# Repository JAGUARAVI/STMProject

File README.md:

# ESWCap — STM32G474

Port of the **ESWCap** autoranging capacitance meter (originally ESP32-S3 / ESP-IDF)
to an **STM32G474CEU6**, targeting the **WeAct Studio "Long" core board**.

> **Status: firmware implemented, not yet run on silicon.** C-mode (RC-step +
> comparator oscillator), autoranging, fusion, calibration, the console and the
> `@@EVT` protocol are complete. R-mode (Kelvin/TIA) is implemented for the
> combined board and is compile-time gated behind `ESWCAP_HAS_RMODE`; the
> default build refuses `mode r` until the Q1/LMC6482/K1/K2/OPAMP3 hardware is
> fitted. See `docs/handoff-verdict.md` for the topology review and
> `docs/port-plan.md` §6 for bring-up.

---

## Target hardware

| Property | Value |
| --- | --- |
| Board | WeAct Studio STM32G474CEU6 "Long" core board |
| MCU | STM32G474CEU6 — Cortex-M4F, 170 MHz |
| Package | UFQFPN48 (48 pins) |
| Flash | 512 KB |
| SRAM | 128 KB |
| HSE crystal | 8 MHz, on **PF0/PF1** (not PA) |
| Regulator | ME6231A33M3G (5 V pin accepts ~3.5–18 V) |
| User LED | **PC6**, active high (`PC6 -> 5.1k -> LED -> GND`) |
| User button | **PC13**, active **high** (`PC13 -> 330R -> key -> 3.3 V`) |

Board repo (schematics, datasheets, examples):
<https://github.com/WeActStudio/WeActStudio.STM32G474CoreBoard>

### Carrier PCB (Rev B)

The combined C+R front end is built as a 111 × 85 mm, 2-layer carrier under the
WeAct Long module.  The module plugs into two rows of 2.54 mm sockets; the
analog front end, relays, SSRs, DUT/bias terminals and console header are on the
carrier.

| Item | Value |
| --- | --- |
| Schematic | `~/Documents/KiCad/Project/Project.kicad_sch` (KiCad 10) |
| PCB | `~/Documents/KiCad/Project/Project.kicad_pcb` |
| Fab outputs | `~/Documents/KiCad/Project/fab/` (Gerbers, drill, BOM, PnP) |
| Design record | [`docs/pcb-design.md`](docs/pcb-design.md) |
| DRC | 0 errors, 0 unconnected, 25 silkscreen-only warnings |
| Module pin order | P1/P2 pin 1 at the **right** end; P3/P4 four leftmost pins |
| Rev B fixes | D6 body-diode block, C1 35 V bipolar, R9 47 Ω, C3 to VREF, console J7, per-IC decoupling, fail-safe pulls |

The module's +5 V comes from USB VBUS (P3-4); the relay coils need USB power.

### Peripheral availability on the 48-pin package

Verified against the STM32G474CE pin database (UFQFPN48). The analog peripherals
are **better** here than the 48-pin pin count suggests — the earlier assumption
that the internal analog is unusable was wrong.

**Comparators — all 7 are bonded out.** Each `INM` can be driven internally by a
DAC, so the comparator reference needs no external divider.

| | `INP` | `INM` options | Internal DAC on `INM` | Output pins (AF8) |
| --- | --- | --- | --- | --- |
| COMP1 | PA1, PB1 | PA0, PA4 | **DAC1_CH1, DAC3_CH1** | PA0, PA6, PA11, PB8 |
| COMP2 | PA3, PA7 | PA2, PA5 | **DAC1_CH2, DAC3_CH2** | PA2, PA7, PA9, PA12 |
| COMP3 | PA0 | PF1 *(HSE!)* | DAC1_CH1, DAC3_CH1 | PB7, PB15 (AF3) |
| COMP4 | PB0 | PB2 | **DAC1_CH1, DAC3_CH2** | PB1, PB6, PB14 |
| COMP5 | PB13 | PB10 | DAC1_CH2, DAC4_CH1 | PA9 |
| COMP6 | PB11 | PB15 | DAC2_CH1, DAC4_CH2 | PA10, PC6 (AF7) |
| COMP7 | PB14 | PB12 | DAC2_CH1, DAC4_CH1 | PA8 |

**OPAMPs — 1, 2 and 3 are bonded out** (USB is on PA11/PA12, not PA2/PA3).
`InternalOutput` routes `VOUT` straight to an ADC channel with **no pin**:

| | `VINP` | Internal `VINP` | `VINM` | `VOUT` pin | `VOUT`→ADC (internal) |
| --- | --- | --- | --- | --- | --- |
| OPAMP1 | PA1, PA3, PA7 | **DAC3_CH1** | PA3 | PA2 | ADC1_IN13 |
| OPAMP2 | PA7, PB14, PB0 | — | PA5 | PA6 | ADC2_IN16 |
| OPAMP3 | PB0, PB13, PA1 | **DAC3_CH2** | PB2, PB10 | PB1 | ADC2_IN18, ADC3_IN13 |

OPAMP4/5/6 need PD/PE pins that do not exist on the 48-pin package.

**ADCs** — 5 instances, channels available:

* `ADC1`: PA0(IN1), PA1(IN2), PA2(IN3), PA3(IN4), PB0(IN15), PB1(IN12),
  PB11(IN14), PB12(IN11), PB14(IN5), PF0(IN10)
* `ADC2`: PA0(IN1), PA1(IN2), PA4(IN17), PA5(IN13), PA6(IN3), PA7(IN4),
  PB11(IN14), PB15(IN15), PB2(IN12), PC4(IN5), PF1(IN10)
* `ADC3`: PB0(IN12), PB1(IN1), PB13(IN5)
* `ADC4`: PB12(IN3), PB14(IN4), PB15(IN5)
* `ADC5`: PA8(IN1), PA9(IN2)

**DAC — 4 instances, but only DAC1/DAC2 have pins:**

| | Pin output | Internal-only use | Max rate |
| --- | --- | --- | --- |
| DAC1 | `OUT1 = PA4`, `OUT2 = PA5` | COMP1/3/4, COMP2/5 | 1 MSPS |
| DAC2 | `OUT1 = PA6` | COMP6/7 only | 1 MSPS |
| **DAC3** | **none** | **COMP1/3, COMP4, OPAMP1, OPAMP3, OPAMP6** | 15 MSPS |
| **DAC4** | **none** | COMP5/7, COMP6, OPAMP4, OPAMP5 | 15 MSPS |

**DAC3/DAC4 are internal-only by design** — they exist purely to feed comparators
and op-amps with no pin at all. That is a significant asset for this project:
**two extra 12-bit threshold sources at zero pin cost.** Prefer them for the
comparator reference so PA4/PA5 stay free.

**Reference:** pin 20 is a dedicated **`VREF+`** — a clean external reference can
be fitted instead of relying on VDDA. `VREFBUF` (2.048 / 2.5 / 2.9 V) is also
available but draw only ~6.5 mA and needs 1 µF + 100 nF at the pin.

#### Comparator → timer routing (the key capability)

A comparator output can reach a timer's input capture **internally, with no pin**.
This is what lets the ESP32's software ISR be replaced by hardware period
measurement. Routing flexibility differs sharply by timer:

| Timer | Width | COMPs accepted on `TI1` | Notes |
| --- | --- | --- | --- |
| **TIM2** | **32-bit** | **COMP1…COMP7** | Best choice: no overflow bookkeeping to 25 s |
| TIM3 | 16-bit | COMP1…COMP7 | Also very flexible |
| TIM4 | 16-bit | COMP1…COMP7 | |
| TIM1/TIM8/TIM20 | 16-bit | COMP1…COMP4 only | `TI2/3/4` accept no comparator |

**Recommendation: `COMP1_OUT` → `TIM2_CH1` input capture.** TIM2 is 32-bit, accepts
any comparator on `TI1`, and at 170 MHz gives 5.88 ns resolution with a 25.3 s
wrap — covering the whole 10 Hz…1 MHz oscillator band in one timer, unpowered by
CPU jitter.

#### Real constraints to plan around

* **`INM` and the DAC output share pins.** `PA4` is both `DAC1_OUT1` and
  COMP1's `INM`; `PA5` is both `DAC1_OUT2` and COMP2's `INM`. Using the internal
  DAC costs those pins. **Use DAC3 instead** to avoid the conflict entirely.
* **Comparator output must not land on its own input pin.** COMP1's output
  shares PA0 with its `INM`; COMP2's shares PA2 with its `INM`. Pick a different
  output (COMP2 → PA7/PA9) — or better, route it internally to the timer and use
  **no output pin at all**. COMP1's output exists **only on PA0, PA6, PA11 and
  PB8** (not PA8 — PA8's AF8 is COMP7_OUT). PA11 is USB and PB8 is BOOT0, so
  in practice it is PA0 or PA6.
* **OPAMP1 `VOUT` (PA2) overlaps COMP2's `INM`**, and OPAMP2 `VOUT` (PA6)
  overlaps COMP1's output. Mode-dependent, but allocate deliberately.
* **`OPAMP_NONINVERTINGINPUT_DAC` and `..._IO3` are the same bit encoding**
  (`OPAMP_CSR_VPSEL`). Which one is active is per-instance. Set it deliberately.
* **No OPAMP→OPAMP and no OPAMP→COMP internal chaining** on G4. Internal chains
  are only `DAC→COMP`, `DAC→OPAMP`, `OPAMP→ADC`.
* **No `DAC→ADC` direct channel.** To read a DAC internally, route it through an
  op-amp: `DAC3_CHx → OPAMP(follower) → ADC` (all internal).
* **No comparator window mode on G4** (contrary to many blog posts) and **no
  clocked comparator output filter** — only programmable hysteresis and
  timer-based blanking.
* **COMP3's only `INM` is `PF1`, which is the HSE crystal pin.** COMP3 is
  effectively unusable while the external crystal is fitted.
* **Reserved:** PA13/PA14 (SWD), PC6 (user LED), PC13 (user button),
  PF0/PF1 (HSE crystal), PA11/PA12 (USB D−/D+), PB8 (BOOT0).

### Replacing the LM393 with COMP1 — strongly recommended

The external LM393 oscillator can be replaced by **COMP1** entirely. The
comparator's `INM` can be driven by `DAC1_CH1` internally, so the external
reference divider (10 kΩ/10 kΩ), the 100 kΩ hysteresis resistor and the 10 kΩ
pull-up all disappear with the chip.

Suggested mapping (avoiding the collisions above):

| Function | Pin | Notes |
| --- | --- | --- |
| COMP1 `INP` | **PB1** | `V_cap` sense node (BAT54S clamped) |
| COMP1 `INM` | internal | `DAC1_CH1` — replaces the 1.65 V divider |
| `DAC1_OUT1` | PA4 | leave unrouted, or reserve |
| COMP1 `OUT` | **PA0** or **PA6** | drive-buffer input; timer capture is internal |

Why this is an upgrade, not just a part-count reduction:

* **Programmable hysteresis.** The LM393's hysteresis is fixed by the 100 kΩ
  feedback resistor. COMP1 sets hysteresis on a 0–1023 scale in software, so it
  can be tuned **per range** instead of one compromise value.
* **Timer input-capture replaces the ISR.** Route `COMP1_OUT` to a timer's
  capture input and the period is measured in hardware. This directly addresses
  the *"ISR Latency Profiling"* pending item in the ESP32 `HANDOVER.md` — the
  ESP32's software oscillator loop put CPU jitter straight into the timing.
* **The rate limiter becomes unnecessary.** `OSC_MIN_EDGE_INTERVAL_US = 3`
  exists because the ESP32 ISR had to mirror the comparator output back to the
  drive pin, so a too-fast loop could freeze the device. With COMP1 driving the
  timing directly, a too-fast loop self-limits rather than hanging the CPU.
* **Far faster.** G4 comparator propagation is ns-class versus the LM393's
  ~1.3 µs, which is what actually limited the sub-100 pF ranges.

This does not change the *physics* of `T = K·R·C + T0`, so the existing `K`/`T0`
calibration model carries over unchanged.

---

## Toolchain

| Component | Version / location |
| --- | --- |
| PlatformIO Core | 6.2.0 — `~/.platformio/penv/bin/pio` |
| STM32 platform | `ststm32` 20.0.0 |
| Framework | **STM32Cube HAL/LL** (`framework = stm32cube`) |
| Toolchain | `arm-none-eabi-gcc` 7.2.1 (installed by PlatformIO) |
| Upload | **USB DFU** bootloader via `dfu-util` |
| Debug | Optional — ST-Link / SWD (see below) |

PlatformIO Core is installed under `~/.platformio/penv` and is **not on the
default PATH**. The project's `.vscode/settings.json` prepends it for integrated
terminals. For your own shell:

```bash
export PATH="$HOME/.platformio/penv/bin:$PATH"
```

---

## Build, upload, monitor

```bash
pio run                      # build (default env: weact_g474ceu6)
pio run -t upload            # flash over USB DFU
pio device monitor -b 115200 # serial console, USART1 on PA9/PA10
```

> **Console wiring:** the WeAct Long board has **native USB only** (PA11/PA12);
> there is no on-board USB-UART bridge. The Type-C port is for DFU/programming.
> For the console, connect an external 3.3 V USB-UART adapter to the P1 header:
> adapter TX -> **PA10**, adapter RX -> **PA9**, GND -> GND. Do not connect the
> adapter's 3.3 V if the board is already powered.

### Flashing over USB DFU

The board ships with ST's ROM DFU bootloader. No probe is required.

1. Hold **BOOT0**, then tap **NRST**, then release **BOOT0**.
2. The board enumerates as ST's ROM bootloader — USB ID `0483:DF11`.
3. Run `pio run -t upload`. PlatformIO adds the DFU suffix to `firmware.bin`
   automatically and flashes it with `dfu-util`.
4. Reset (or power-cycle) to run the firmware.

Check the device is visible:

```bash
lsusb | grep -i 0483        # expect: 0483:df11 STMicroelectronics STM32 BOOTLOADER
dfu-util -l                 # lists DFU interfaces
```

If `dfu-util` reports no device, the board is not in DFU mode, or the udev rules
do not grant access (see **udev** below).

### Debugging over SWD (optional)

DFU cannot debug. To single-step, watch variables or use breakpoints, attach a
probe to the SWD header and use the debug environment:

```bash
pio run  -e weact_g474ceu6_debug -t upload   # upload over SWD
pio debug -e weact_g474ceu6_debug            # start a debug session
```

This env is built with `-DDEBUG -DUSE_FULL_ASSERT` and flashes via `stlink`.

---

## Environments

| Environment | Framework | Upload | Purpose |
| --- | --- | --- | --- |
| `weact_g474ceu6` | stm32cube | **dfu** | Default. C-mode-only build; flash over USB. |
| `weact_g474ceu6_debug` | stm32cube | stlink | `-DDEBUG -DUSE_FULL_ASSERT`, for GDB/Live Watch. |
| `weact_g474ceu6_stlink` | ststm32 | stlink | Release build, flashed via an SWD probe. |
| `weact_g474ceu6_combined` | stm32cube | dfu | `-DESWCAP_HAS_RMODE=1`; requires the Q1/LMC6482/K1/K2/OPAMP3 front end. |

The combined board is a **compile-time** choice on purpose: the default build
must not energise relay coils or drive a Q1 gate that is not fitted. `mode r`
refuses with a clear message until `ESWCAP_HAS_RMODE=1`.

---

## IDE setup

The project is configured for **VS Code** (and compatible forks).

1. Install the recommended extensions — VS Code prompts on open, or run
   *Extensions: Show Recommended Extensions*:
   * `platformio.platformio-ide` (required)
   * `ms-vscode.cpptools` (required by PlatformIO IDE for IntelliSense)
2. Open this folder. PlatformIO indexes the project and writes
   `.vscode/c_cpp_properties.json`, which supplies all Cube HAL include paths
   and the `STM32G474xx` define automatically.
3. Build once (`pio run`) to populate IntelliSense and the compile database.

`.vscode/settings.json` is committed and already handles:

* `pio` on the integrated-terminal PATH,
* C standard / IntelliSense mode (`gcc-arm`),
* serial monitor defaults (115200, DTR/RTS de-asserted),
* excluding `.pio/` from search and the explorer.

`.vscode/c_cpp_properties.json` is gitignored — it is regenerated by PlatformIO
after each build and contains absolute paths. `.vscode/launch.json` **is**
committed, because DFU cannot debug and so PlatformIO never generates it for
this setup.

### udev rules (Linux, for DFU and probes)

PlatformIO's own rules file is already installed at
`/etc/udev/rules.d/99-platformio-udev.rules`, which covers ST-Link and the STM32
DFU bootloader. If `dfu-util` cannot open the device, reinstall them:

```bash
curl -fsSL https://raw.githubusercontent.com/platformio/platformio-core/develop/platformio/assets/system/99-platformio-udev.rules \
  | sudo tee /etc/udev/rules.d/99-platformio-udev.rules
sudo udevadm control --reload-rules && sudo udevadm trigger
```

Then unplug/replug the board. Note this system has no `plugdev` group; if access
still fails, add a rule scoped to your user or group.

---

## Firmware architecture

The ESP32 build was 4 000 lines in one file. This port splits it so the maths is
testable on a host and the hardware access is confined to one layer.

```
src/
  main.c              entry point (nothing else)
  app.c               cooperative scheduler: the only place that decides when to measure
  bsp/                hardware layer — the only code that touches HAL/registers
    bsp.c             170 MHz PLL from HSE, SysTick, DWT, IWDG, USB clock
    bsp_console.c     USART1 interrupt-driven RX, line assembly, printf
    bsp_adc.c         ADC1 stream (TIM6+DMA+oversampling), ADC2/3/4 single reads, VREFINT
    bsp_comp.c        COMP1 + DAC3 + TIM2 TISEL capture; COMP4 overvoltage guard
    bsp_frontend.c    SSR/relay/mux control, safety state machine, mode interlock
    bsp_dac.c         DAC3_CH1 (COMP1) and DAC1_CH1 (COMP4), both internal-only
    bsp_opamp.c       OPAMP1: R-mode Kelvin error amplifier (VINP=B, VINM=VREF)
    bsp_opamp3.c      OPAMP3: V_N unity-gain buffer
    bsp_store.c       flash record store (NVS replacement)
    bsp_led.c         PC6 software-PWM status LED
  measure/            pure arithmetic — no HAL, host-testable
    rc_fit.c          voltage-domain Gauss-Newton exponential fit
    osc_calc.c        T = K*R*C + T0 model and its solvers
    board.c           board constants and the C_block series transform
    adc_measure.c     curve -> scored sample (fit, gates, quality)
    osc_measure.c     period -> scored sample
    fusion.c          median gate and log-domain weighted fusion
    autorange.c       PROBE -> SWEEP -> FUSION pipeline
    rmode.c           4-wire Kelvin / TIA resistance (BSP-facing)
    rmode_math.c      pure Kelvin/TIA arithmetic (host-tested)
  calib/calib.c       calibration state, solvers, flash record
  proto/
    events.c          @@EVT JSON telemetry (contract preserved)
    console_cmds.c    the command set
```

What the hardware changed, relative to the ESP32:

| ESP32 mechanism | G474 mechanism |
| --- | --- |
| Software ADC poll loop + adaptive decimation | TIM6-triggered ADC1 + circular DMA, hardware oversampling |
| LM393 + 10k/10k divider + 100k hysteresis | COMP1 + DAC3 internal threshold (70 mV hysteresis, K ≈ 0.085) |
| ISR mirrors comparator, PCNT measures it | **No CPU in the loop**: COMP1_OUT/PA0 drives the buffer; TIM2 captures via TISEL |
| NVS blob store | reserved 2 KB flash page, append-only CRC records |
| WS2812 over RMT | PC6 software PWM, same operational language |

## Testing

The measurement maths compiles and runs on the build machine:

```bash
make -C test/host        # builds and runs the unit tests
```

21 tests cover the exponential fit (including its insensitivity to a biased
asymptote), the C_block transform, the oscillator model and two-point solve, ADC
and oscillator sample scoring, fusion gating and log-domain averaging, both
calibration solvers, the Kelvin/TIA resistance equations, and the R-mode
calibration setters. They run against
the **same source files** the firmware uses; only the flash store is stubbed.

---

## Repository layout

```
platformio.ini          Build/upload/debug configuration (3 environments)
src/main.c              Entry point
src/app.c               Scheduler
src/bsp/                Hardware layer
src/measure/            Measurement maths (HAL-free)
src/calib/              Calibration state and solvers
src/proto/              Telemetry and console
include/                Public headers, pin map (config.h), stm32_assert.h
test/host/              Host unit tests (make -C test/host)
docs/                   Port plan, peripheral reference, design notes
.vscode/                Editor configuration
```

---

## Documentation

| Document | Purpose |
| --- | --- |
| **`docs/port-plan.md`** | **The port plan.** Audit of the ESP32 firmware, the G474 architecture it maps to, the document rework list, and the phased build sequence. Start here. |
| **`docs/peripherals-g474.md`** | Verified peripheral facts — ADC/COMP/DAC/OPAMP/timer/storage, plus the ES0430 errata that constrain the code. |
| **`docs/handoff-verdict.md`** | **Review of the other agent's handoff**: what it gets right, what is unsafe to apply literally, what the previous firmware got wrong, and the corrected pin map. Read with the R-mode work. |
| `docs/kelvin-ohmmeter-g474.md` | R-mode electrical design. Superseded banner + corrected topology, pin map and equations. |
| `docs/resistance-autoranging-plan.md` | R-mode autoranging + Kelvin/TIA topology. The topology is adopted; the pin table is corrected by the verdict. |

The two R-mode notes were written for a **100-pin G474VE**. They remain useful for
the *electrical* design (sensing topology, ratiometric maths, error budget,
interlock rules); their pin maps and internal-peripheral assumptions have been
corrected in place against the verified 48-pin data.

---

## Next steps

The firmware is complete; what remains needs the physical board.

1. **Verify the pin map against the actual front-end wiring.** `include/config.h`
   is the single source of truth. The switch polarities (SSR/relay active-high,
   MAX4619 EN active-low) are isolated behind three constants in
   `bsp_frontend.c`. The R-mode pins are only meaningful once the combined board
   is fitted.
2. **Flash and confirm the platform comes up.** Expect the banner, `SYSCLK
   170000000 Hz`, and a plausible `VDDA` reading. A blink-code loop at boot
   identifies which `require()` failed (1 = clocks … 8 = R-mode analog).
3. **Verify the ADC stream.** A known DC level on `V_cap` should read correctly,
   and the sample period should match the requested period (scope PA0 for the
   comparator, or trigger on a GPIO toggle).
4. **Verify the comparator.** Inject a square wave on the DUT node and confirm
   the console's `status`/`probe` see oscillation and that `zero` produces a
   stable `T0`. This is the step that proves `TISEL` routing works on silicon.
5. **Calibrate.** `mode c`, then `zero`, `cal1`/`cal2` with 1 % C0G/NP0
   references, `adccal1`/`adccal2` with film references. Record the new `T0`;
   it should be smaller than the ESP32 value because no ISR latency remains.
6. **R-mode bring-up.** Build `weact_g474ceu6_combined` (it sets
   `ESWCAP_HAS_RMODE=1`), flash, `discharge`, `mode r`, then `res`. Check
   V_B ~= 405 mV on a 1 kohm DUT before trusting the top element or the TIA.
   On a C-mode-only board the default build refuses `mode r` instead of
   energising relays that do not exist.

See `docs/port-plan.md` §6 for the phase-by-phase acceptance criteria and §7
for the risk list.

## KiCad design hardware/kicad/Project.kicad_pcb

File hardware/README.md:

# ESWCap Rev C.1 hardware

This directory contains the KiCad source for the Rev C carrier with the
accuracy-plan changes applied (**Rev C.1**, see `docs/accuracy-plan.md`):
USB-only power, 3.3 V relays, true 4-wire C/R, the corrected J8 bias header,
and the H1–H6 accuracy changes.

## Status (2026-11-13)

- **Schematic:** Rev C + accuracy plan H1–H6. ERC-clean (0 errors, 0 warnings).
  - H1 J2-13 (PA7, OPAMP1 sense) moved FL → `MUXR_COM`
  - H2 `MUXR_EN` moved J2-17 (PB2) → J1-17 (PB15)
  - H3 `VBUF` also on J2-17 (PB2, OPAMP3 VINM0) for the PGA stage
  - H4 R20 100k → 1k; H5 D1 BAT54S → BAV199; H6 R33 1M → 10M
  - PWR_FLAGs excluded from BOM/board
- **PCB:** `kicad/Project.kicad_pcb`, 111 × 85 mm, 2 layers, **fully routed**.
  DRC: 0 unconnected, 0 clearance/short/hole errors, schematic parity clean;
  45 silkscreen-only warnings. Critical analog nets are hand-routed and locked;
  the rest is Freerouting + targeted fixes. How it was built:
  `scripts/README.md`.
  - Ground: B.Cu plane + F.Cu pour, stitched by ~318 vias, with **no-pour
    cutouts** under J5/SH divider/U9/U10, the VCAP node, and the TIA input (P2)
  - TIA guard: F.Cu `VBIAS` pour around the U1A summing node (P1)
  - Footprint fixes: C1 and J5/J6 courtyards/silkscreen now match the real
    bodies (they were drawn around the pads only)
- **Fab outputs:** `fab/Project-gerbers.zip` (`fab/gerbers/`), drill + map,
  `fab/Project-pos.csv`, `fab/Project-bom.csv`, schematic PDF/SVG,
  `fab/Project-pcb-front.pdf` / `-back.pdf`, `fab/Project-3d-top.png`.
  **Not yet reviewed by a person — review before ordering.**
- `wip/Project-revC-routing-baseline.kicad_pcb` is the old pre-review baseline,
  kept for reference only. Do not fabricate it.

Open `kicad/Project.kicad_pro` with KiCad 10. The project-local libraries
(`eswcap.kicad_sym`, `eswcap.pretty/`) are included; the schematic will not
resolve symbols/footprints without them.

## Rev C circuit summary

- **Power:** USB-C VBUS → module D4 → VDD5V → module ME6231A33M3G LDO → +3.3 V.
  J3-3/4 (`VDD5V`) are NC on the carrier. No 5 V carrier rail. Only Vbias
  (0–20 V) is external, on J6.
- **Relays:** K1/K2 = Omron **G6S-2 DC3** (3 V coils) on +3.3 V. D4/D5
  flyback cathodes, C10/C15, and coil high side are on +3V3.
- **DUT:** J5 is 4-pin, ordered **FH, SH, SL, FL**. R-mode is true 4-wire
  Kelvin; `SL` has a 100 kΩ series resistor (R40) into U1B.
- **C-mode 4-terminal sense:** 10 M/1 M divider on `SH` (R38/R39), compensated
  by C21 10 pF across the top leg and C20 100 pF across the bottom leg. The
  divider is buffered by the **internal STM32 OPAMP3** (no second LMC6482).
  U9 isolates the `SH → R20 → VN_SENSE` branch when K1 is off; U10 connects
  `SH_DIV` to `VN_SENSE` when K1 is off. U10 is controlled by PC4
  (`C_MODE_SW`, active low).
- **R20 / D2:** R20 = 100 kΩ; D2 = BAV199 (low-leakage clamp).
- **J8 bias-control header:**

| Pin | Signal | Module pin | Note |
| --- | --- | --- | --- |
| 1 | `BIAS_SET` | PA4 / J2-10 | TIM3_CH2 PWM, R34 1 k + C16 10 µF |
| 2 | `BIAS_EN` | PA15 / J1-10 | GPIO, R35 10 k pulldown |
| 3 | `BIAS_MON` | **PA8 / J1-15** | ADC5_IN1, R36 1 k + C17 100 nF |
| 4 | GND | — | — |
| 5 | `+3V3` | J4 | future module <50 mA |
| 6 | `BIAS_UART_TX` | PC10 / J1-9 | USART3_TX |
| 7 | `BIAS_UART_RX` | PC11 / J1-8 | USART3_RX |
| 8 | GND | — | — |

- **PA0 is `DRIVE` / COMP1_OUT** (firmware fix of 2026-11-12). PA8 is now free
  and carries `BIAS_MON`. PC4 is the U10 control output.
- **J5 pin order:** 1 FH, 2 SH, 3 SL, 4 FL. Use 1–2 and 3–4 links for a 2-wire
  DUT.

## BOM

`fab/Project-bom.csv` is generated from the schematic. It contains 88 physical
parts, 46 grouped lines and 3 PWR_FLAGs. The only new orderable part type is
J8 (1×8 2.54 mm header) and J5 (4-pin 5.08 mm terminal block); K1/K2 are
G6S-2 DC3. See the CSV for the complete list.

## What is deliberately not here

- The second LMC6482 was removed: it is not available. The C-mode SH divider
  now uses the internal OPAMP3.
- The PCB is not final. It must be regenerated and rerouted after the
  schematic is frozen. The WIP baseline has the pre-U9/U10 netlist and must
  not be fabricated.
- The OLED/button additions proposed in the integration-plan review are not
  part of this revision.

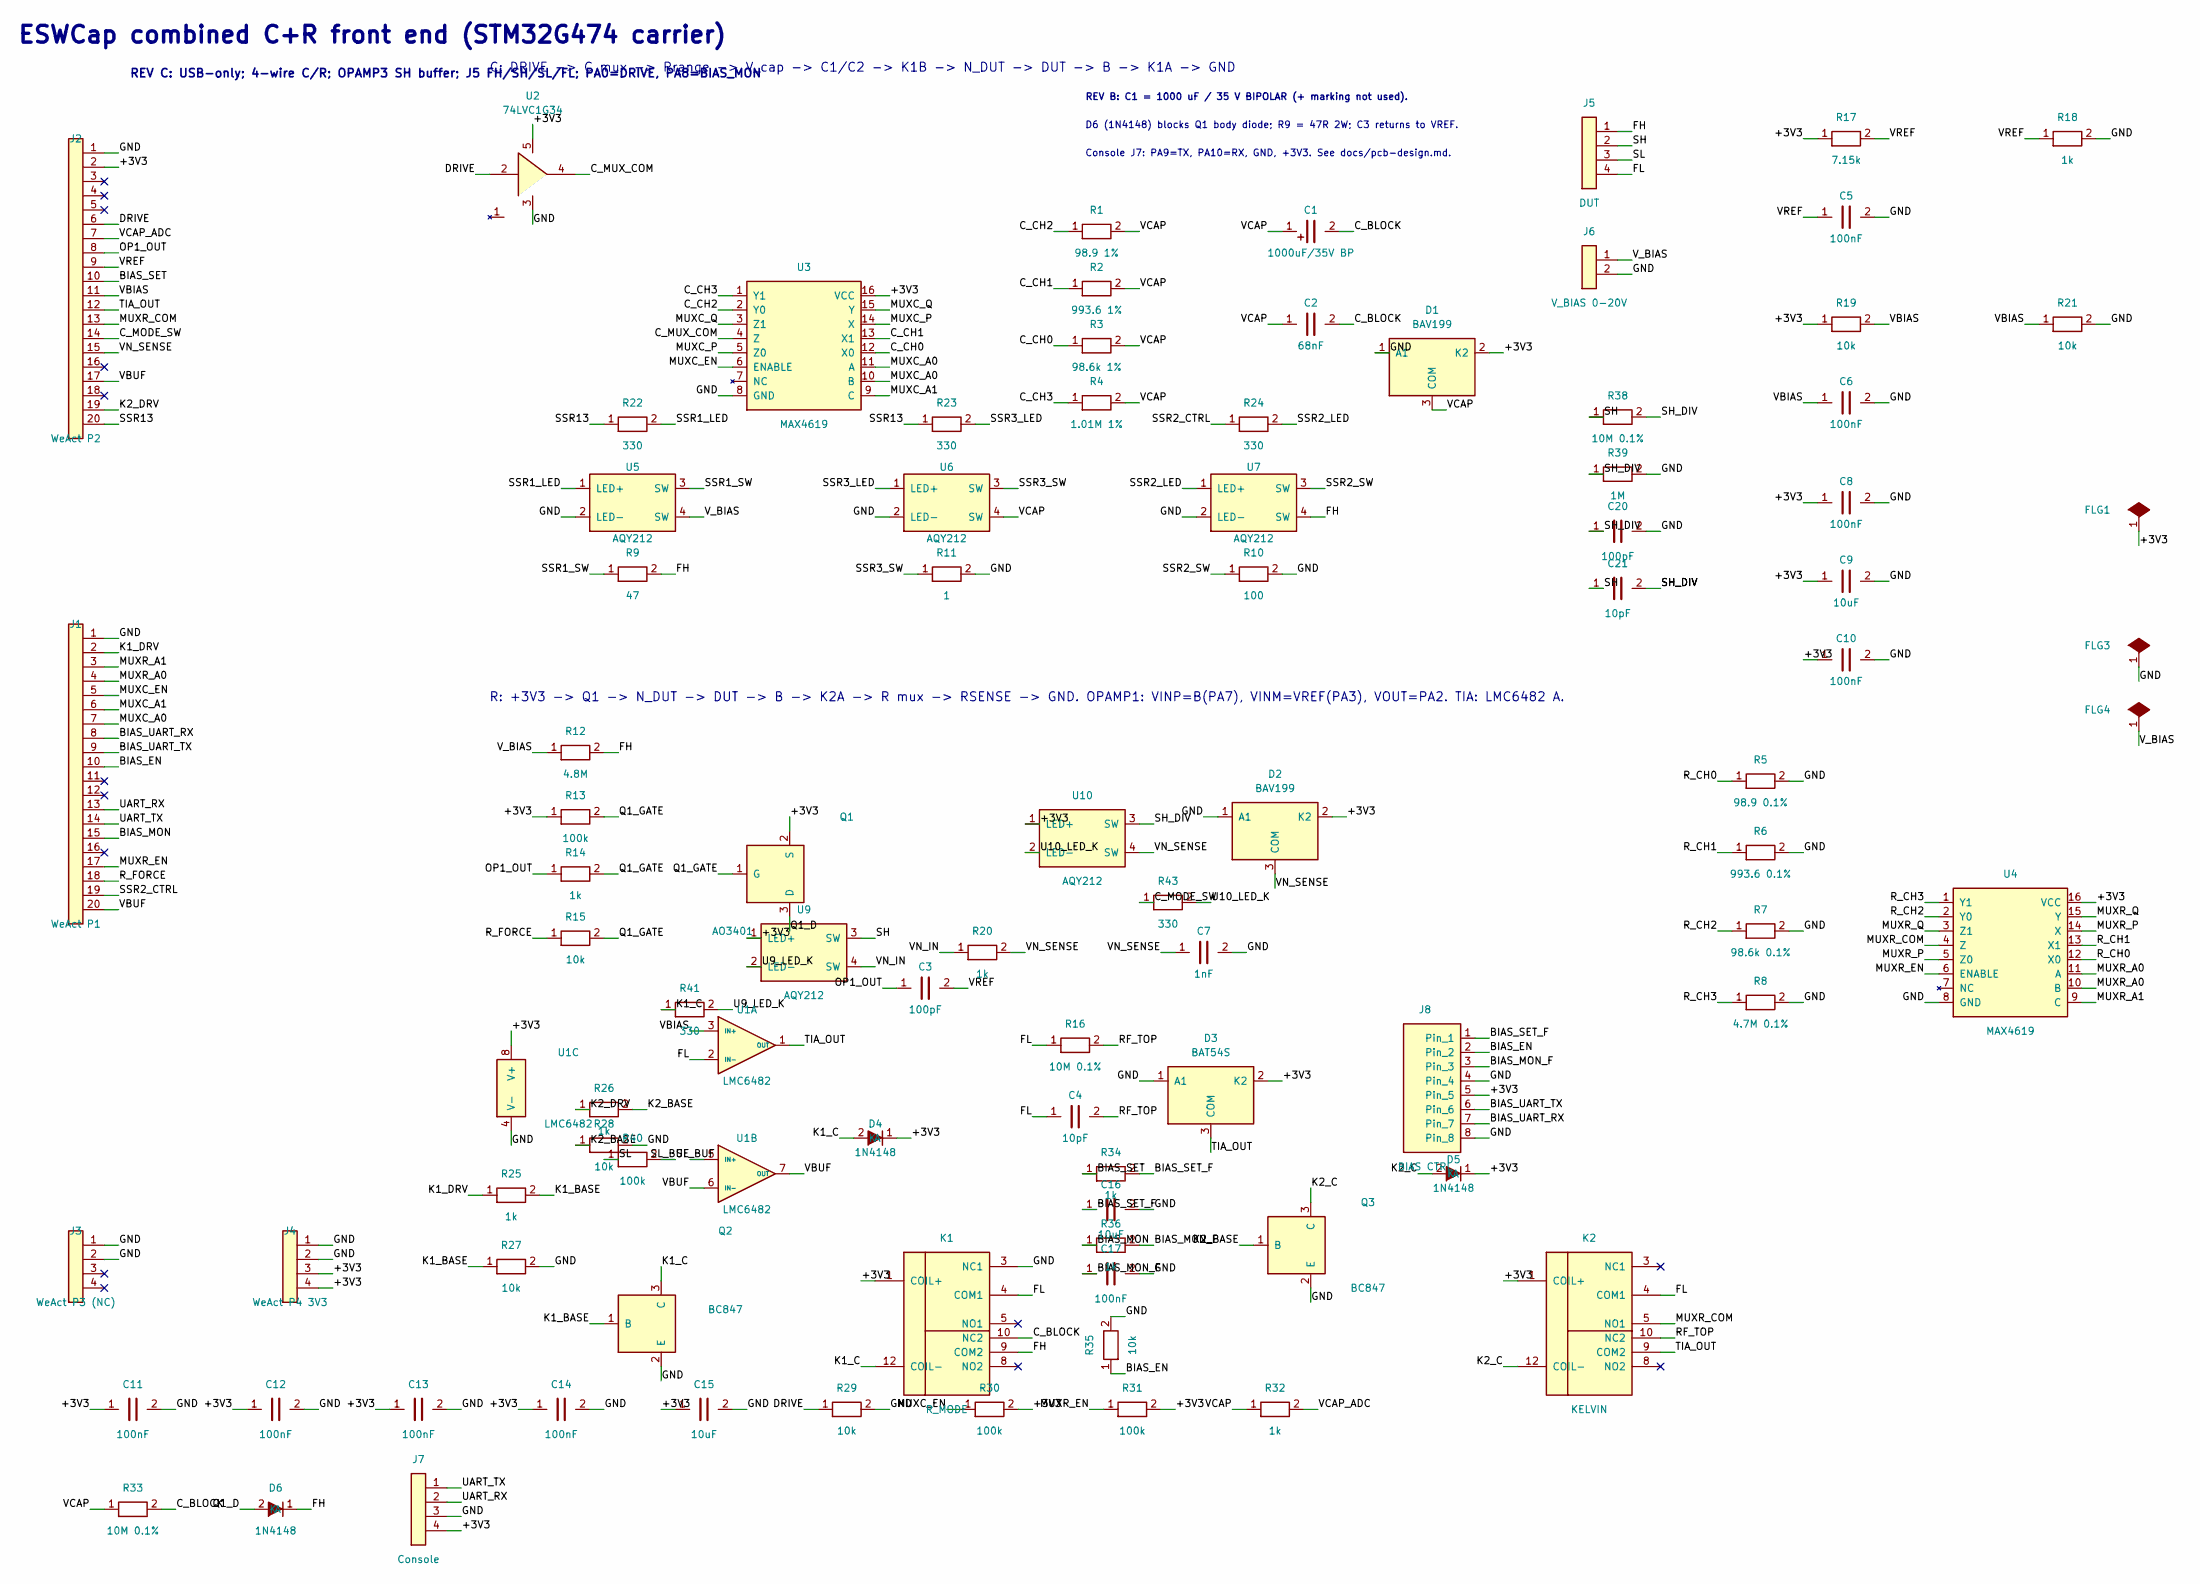
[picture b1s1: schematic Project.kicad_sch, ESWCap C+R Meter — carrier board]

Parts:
C1: 1000uF/35V BP; C_Radial_D16_P7.5
C2: 68nF; C_0805_2012Metric
C3, C20: 100pF; C_0805_2012Metric
C4, C21: 10pF; C_0805_2012Metric
C5, C6, C8, C10, C11, C12, C13, C14, C17: 100nF; C_0805_2012Metric
C7: 1nF; C_0805_2012Metric
C9, C15, C16: 10uF; C_0805_2012Metric
D1, D2: BAV199; SOT-23
D3: BAT54S; SOT-23
D4, D5, D6: 1N4148; D_SOD-123
FLG1, FLG3, FLG4: PWR_FLAG
J1: WeAct P1; PinSocket_1x20_P2.54mm_Vertical
J2: WeAct P2; PinSocket_1x20_P2.54mm_Vertical
J3: WeAct P3 (NC); PinSocket_1x04_P2.54mm_Vertical
J4: WeAct P4 3V3; PinSocket_1x04_P2.54mm_Vertical
J5: DUT; TerminalBlock_4P_5.08
J6: V_BIAS 0-20V; TerminalBlock_2P_5.08
J7: Console; PinSocket_1x04_P2.54mm_Vertical
J8: BIAS CTRL; PinHeader_1x08_P2.54mm_Vertical
K1: R_MODE; Relay_DPDT_Omron_G6S-2; MPN G6S-2 DC3
K2: KELVIN; Relay_DPDT_Omron_G6S-2; MPN G6S-2 DC3
Q1: AO3401; SOT-23
Q2, Q3: BC847; SOT-23
R1: 98.9 1%; R_0805_2012Metric; Tolerance 1%
R2: 993.6 1%; R_0805_2012Metric; Tolerance 1%
R3: 98.6k 1%; R_0805_2012Metric; Tolerance 1%
R4: 1.01M 1%; R_0805_2012Metric; Tolerance 1%
R5: 98.9 0.1%; R_0805_2012Metric; Tolerance 0.1%
R6: 993.6 0.1%; R_0805_2012Metric; Tolerance 0.1%
R7: 98.6k 0.1%; R_0805_2012Metric; Tolerance 0.1%
R8: 4.7M 0.1%; R_0805_2012Metric; Tolerance 0.1%
R9: 47; R_2512_6332Metric
R10: 100; R_2512_6332Metric
R11: 1; R_0805_2012Metric
R12: 4.8M; R_0805_2012Metric
R13, R30, R31, R40: 100k; R_0805_2012Metric
R14, R18, R20, R25, R26, R32, R34, R36: 1k; R_0805_2012Metric
R15, R19, R21, R27, R28, R29, R35: 10k; R_0805_2012Metric
R16: 10M 0.1%; R_0805_2012Metric; Tolerance 0.1%
R17: 7.15k; R_0805_2012Metric
R22, R23, R24, R41, R43: 330; R_0805_2012Metric
R33, R38: 10M 0.1%; R_0805_2012Metric
R39: 1M; R_0805_2012Metric
U1: LMC6482; SOIC-8_3.9x4.9mm_P1.27mm
U2: 74LVC1G34; SOT-23-5
U3, U4: MAX4619; SOIC-16_3.9x9.9mm_P1.27mm
U5, U6, U7, U9, U10: AQY212; DIP-4_W7.62mm

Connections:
/+3V3: C8.1, C9.1, C10.1, C11.1, C12.1, C13.1, C14.1, C15.1, D1.2 (K2), D2.2 (K2), D3.2 (K2), D4.1 (K), D5.1 (K), FLG1.1, J2.2, J4.3, J4.4, J7.4, J8.5, K1.1 (COIL+), K2.1 (COIL+), Q1.2 (S), R13.1, R17.1, R19.1, R30.2, R31.2, U1.8 (V+), U2.5 (VCC), U3.16 (VCC), U4.16 (VCC), U9.1 (LED+), U10.1 (LED+)
/BIAS_EN: J1.10, J8.2, R35.1
/BIAS_MON: J1.15, R36.1
/BIAS_MON_F: C17.1, J8.3, R36.2
/BIAS_SET: J2.10, R34.1
/BIAS_SET_F: C16.1, J8.1, R34.2
/BIAS_UART_RX: J1.8, J8.7
/BIAS_UART_TX: J1.9, J8.6
/C_BLOCK: C1.2 (-), C2.2, K1.10 (NC2), R33.2
/C_CH0: R3.1, U3.12 (X0)
/C_CH1: R2.1, U3.13 (X1)
/C_CH2: R1.1, U3.2 (Y0)
/C_CH3: R4.1, U3.1 (Y1)
/C_MODE_SW: J2.14, R43.1
/C_MUX_COM: U2.4 (Y), U3.4 (Z)
/DRIVE: J2.6, R29.1, U2.2 (A)
/FH: D6.1 (K), J5.1, K1.9 (COM2), R9.2, R12.2, U7.4 (SW)
/FL: C4.1, J5.4, K1.4 (COM1), K2.4 (COM1), R16.1, U1.2 (IN-)
/GND: C5.2, C6.2, C7.2, C8.2, C9.2, C10.2, C11.2, C12.2, C13.2, C14.2, C15.2, C16.2, C17.2, C20.2, D1.1 (A1), D2.1 (A1), D3.1 (A1), FLG3.1, J1.1, J2.1, J3.1, J3.2, J4.1, J4.2, J6.2, J7.3, J8.4, J8.8, K1.3 (NC1), Q2.2 (E), Q3.2 (E), R5.2, R6.2, R7.2, R8.2, R10.2, R11.2, R18.2, R21.2, R27.2, R28.2, R29.2, R35.2, R39.2, U1.4 (V-), U2.3 (GND), U3.8 (GND), U4.8 (GND), U5.2 (LED-), U6.2 (LED-), U7.2 (LED-)
/K1_BASE: Q2.1 (B), R25.2, R27.1
/K1_C: D4.2 (A), K1.12 (COIL-), Q2.3 (C), R41.1
/K1_DRV: J1.2, R25.1
/K2_BASE: Q3.1 (B), R26.2, R28.1
/K2_C: D5.2 (A), K2.12 (COIL-), Q3.3 (C)
/K2_DRV: J2.19, R26.1
/MUXC_A0: J1.7, U3.10 (B), U3.11 (A)
/MUXC_A1: J1.6, U3.9 (C)
/MUXC_EN: J1.5, R30.1, U3.6 (ENABLE)
/MUXC_P: U3.5 (Z0), U3.14 (X)
/MUXC_Q: U3.3 (Z1), U3.15 (Y)
/MUXR_A0: J1.4, U4.10 (B), U4.11 (A)
/MUXR_A1: J1.3, U4.9 (C)
/MUXR_COM: J2.13, K2.5 (NO1), U4.4 (Z)
/MUXR_EN: J1.17, R31.1, U4.6 (ENABLE)
/MUXR_P: U4.5 (Z0), U4.14 (X)
/MUXR_Q: U4.3 (Z1), U4.15 (Y)
/OP1_OUT: C3.1, J2.8, R14.1
/Q1_D: D6.2 (A), Q1.3 (D)
/Q1_GATE: Q1.1 (G), R13.2, R14.2, R15.2
/RF_TOP: C4.2, K2.10 (NC2), R16.2
/R_CH0: R5.1, U4.12 (X0)
/R_CH1: R6.1, U4.13 (X1)
/R_CH2: R7.1, U4.2 (Y0)
/R_CH3: R8.1, U4.1 (Y1)
/R_FORCE: J1.18, R15.1
/SH: C21.1, J5.2, R38.1, U9.3 (SW)
/SH_DIV: C20.1, C21.2, R38.2, R39.1, U10.3 (SW)
/SL: J5.3, R40.1
/SL_BUF: R40.2, U1.5 (IN+)
/SSR1_LED: R22.2, U5.1 (LED+)
/SSR1_SW: R9.1, U5.3 (SW)
/SSR2_CTRL: J1.19, R24.1
/SSR2_LED: R24.2, U7.1 (LED+)
/SSR2_SW: R10.1, U7.3 (SW)
/SSR3_LED: R23.2, U6.1 (LED+)
/SSR3_SW: R11.1, U6.3 (SW)
/SSR13: J2.20, R22.1, R23.1
/TIA_OUT: D3.3 (COM), J2.12, K2.9 (COM2), U1.1 (OUT)
/U9_LED_K: R41.2, U9.2 (LED-)
/U10_LED_K: R43.2, U10.2 (LED-)
/UART_RX: J1.13, J7.2
/UART_TX: J1.14, J7.1
/VBIAS: C6.1, J2.11, R19.2, R21.1, U1.3 (IN+)
/VBUF: J1.20, J2.17, U1.6 (IN-), U1.7 (OUT)
/VCAP: C1.1 (+), C2.1, D1.3 (COM), R1.2, R2.2, R3.2, R4.2, R32.1, R33.1, U6.4 (SW)
/VCAP_ADC: J2.7, R32.2
/VN_IN: R20.1, U9.4 (SW)
/VN_SENSE: C7.1, D2.3 (COM), J2.15, R20.2, U10.4 (SW)
/VREF: C3.2, C5.1, J2.9, R17.2, R18.1
/V_BIAS: FLG4.1, J6.1, R12.1, U5.4 (SW)

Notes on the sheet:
C: DRIVE -> C mux -> Rrange -> V_cap -> C1/C2 -> K1B -> N_DUT -> DUT -> B -> K1A -> GND
R: +3V3 -> Q1 -> N_DUT -> DUT -> B -> K2A -> R mux -> RSENSE -> GND. OPAMP1: VINP=B(PA7), VINM=VREF(PA3), VOUT=PA2. TIA: LMC6482 A.
ESWCap combined C+R front end (STM32G474 carrier)
REV B: C1 = 1000 uF / 35 V BIPOLAR (+ marking not used).
D6 (1N4148) blocks Q1 body diode; R9 = 47R 2W; C3 returns to VREF.
Console J7: PA9=TX, PA10=RX, GND, +3V3. See docs/pcb-design.md.
REV C: USB-only; 4-wire C/R; OPAMP3 SH buffer; J5 FH/SH/SL/FL; PA0=DRIVE, PA8=BIAS_MON

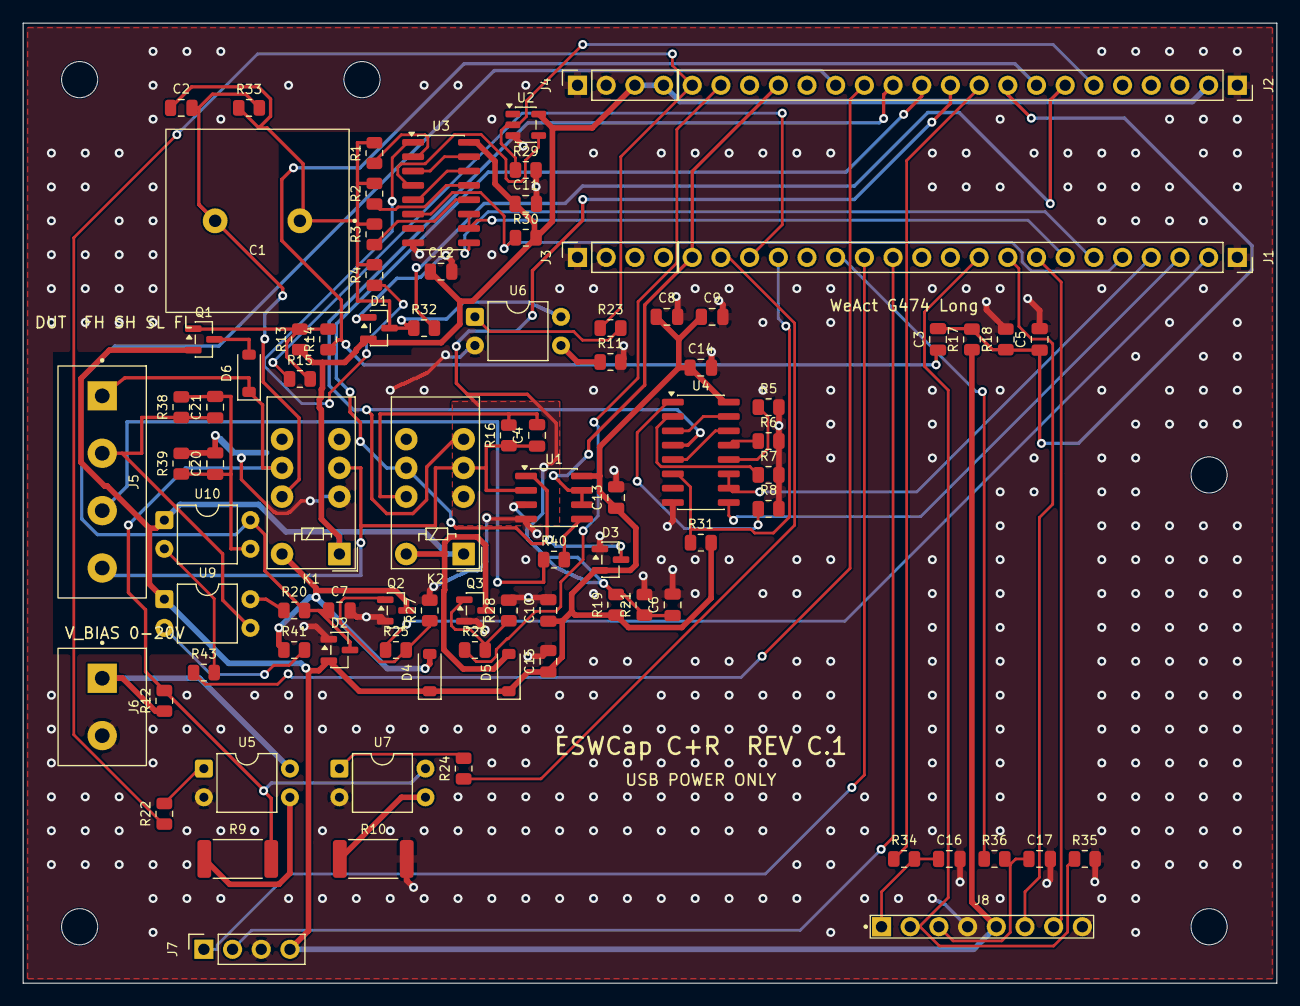
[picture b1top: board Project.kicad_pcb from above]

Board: 2 copper layers, 111.0 x 85.0 mm, 93 parts (0 on the bottom side), 70 nets.

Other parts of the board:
H1, H2, H3, H4, H5: M3; MountingHole_3.2mm_M3

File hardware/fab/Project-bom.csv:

"Refs","Value","Footprint","MPN","Qty"
"C1","1000uF/35V BP","eswcap:C_Radial_D16_P7.5","","1"
"C2","68nF","eswcap:C_0805_2012Metric","","1"
"C3,C20","100pF","eswcap:C_0805_2012Metric","","2"
"C4,C21","10pF","eswcap:C_0805_2012Metric","","2"
"C5,C6,C8,C10-C14,C17","100nF","eswcap:C_0805_2012Metric","","9"
"C7","1nF","eswcap:C_0805_2012Metric","","1"
"C9,C15,C16","10uF","eswcap:C_0805_2012Metric","","3"
"D1,D2","BAV199","eswcap:SOT-23","","2"
"D3","BAT54S","eswcap:SOT-23","","1"
"D4-D6","1N4148","eswcap:D_SOD-123","","3"
"J1","WeAct P1","eswcap:PinSocket_1x20_P2.54mm_Vertical","","1"
"J2","WeAct P2","eswcap:PinSocket_1x20_P2.54mm_Vertical","","1"
"J3","WeAct P3 (NC)","eswcap:PinSocket_1x04_P2.54mm_Vertical","","1"
"J4","WeAct P4 3V3","eswcap:PinSocket_1x04_P2.54mm_Vertical","","1"
"J5","DUT","eswcap:TerminalBlock_4P_5.08","","1"
"J6","V_BIAS 0-20V","eswcap:TerminalBlock_2P_5.08","","1"
"J7","Console","eswcap:PinSocket_1x04_P2.54mm_Vertical","","1"
"J8","BIAS CTRL","eswcap:PinHeader_1x08_P2.54mm_Vertical","","1"
"K1","R_MODE","eswcap:Relay_DPDT_Omron_G6S-2","G6S-2 DC3","1"
"K2","KELVIN","eswcap:Relay_DPDT_Omron_G6S-2","G6S-2 DC3","1"
"Q1","AO3401","eswcap:SOT-23","","1"
"Q2,Q3","BC847","eswcap:SOT-23","","2"
"R1","98.9 1%","eswcap:R_0805_2012Metric","","1"
"R2","993.6 1%","eswcap:R_0805_2012Metric","","1"
"R3","98.6k 1%","eswcap:R_0805_2012Metric","","1"
"R4","1.01M 1%","eswcap:R_0805_2012Metric","","1"
"R5","98.9 0.1%","eswcap:R_0805_2012Metric","","1"
"R6","993.6 0.1%","eswcap:R_0805_2012Metric","","1"
"R7","98.6k 0.1%","eswcap:R_0805_2012Metric","","1"
"R8","4.7M 0.1%","eswcap:R_0805_2012Metric","","1"
"R9","47","eswcap:R_2512_6332Metric","","1"
"R10","100","eswcap:R_2512_6332Metric","","1"
"R11","1","eswcap:R_0805_2012Metric","","1"
"R12","4.8M","eswcap:R_0805_2012Metric","","1"
"R13,R30,R31,R40","100k","eswcap:R_0805_2012Metric","","4"
"R14,R18,R20,R25,R26,R32,R34,R36","1k","eswcap:R_0805_2012Metric","","8"
"R15,R19,R21,R27-R29,R35","10k","eswcap:R_0805_2012Metric","","7"
"R16,R33,R38","10M 0.1%","eswcap:R_0805_2012Metric","","3"
"R17","7.15k","eswcap:R_0805_2012Metric","","1"
"R22-R24,R41,R43","330","eswcap:R_0805_2012Metric","","5"
"R39","1M","eswcap:R_0805_2012Metric","","1"
"U1","LMC6482","eswcap:SOIC-8_3.9x4.9mm_P1.27mm","","1"
"U2","74LVC1G34","eswcap:SOT-23-5","","1"
"U3,U4","MAX4619","eswcap:SOIC-16_3.9x9.9mm_P1.27mm","","2"
"U5-U7,U9,U10","AQY212","eswcap:DIP-4_W7.62mm","","5"

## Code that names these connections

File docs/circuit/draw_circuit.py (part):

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    'C1': '1000 µF 35 V bipolar electrolytic',
    'J1': 'WeAct header P1 (1×20 socket)', 'J2': 'WeAct header P2 (1×20 socket)',
    'J3': 'WeAct header P3 (1×4, NC)', 'J4': 'WeAct header P4 (1×4)',
    'J5': 'DUT, 4-pin 5.08 mm terminal', 'J6': 'V_BIAS 0–20 V, 2-pin 5.08 mm terminal',
    'J7': 'Console, 1×4 socket', 'J8': 'Bias control, 1×8 header',
}

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            for c, s in zip(cols, r):
                T((c, y - i * 0.72), s, fs=FS - 0.5, color='black' if i else BLUE)
        T((0, 5.6), 'TLC2272 / TLC2262 are not used: they need ≥ 4.4 V and the carrier runs on 3.3 V.', fs=FS - 1, color=GREY)
        T((0, 4.9), 'Firmware note: OPAMP3 PGA mode, PC4 (U10), PB15 (MUXR_EN) and PB2 (VBUF) follow docs/accuracy-plan.md F1–F3 (firmware update pending).', fs=FS - 1, color=RED)
        legend(0, 3.6)
        for r in ('U1', 'K1', 'K2', 'J5'):
            SEEN.add(r)
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        d.config(fontsize=FS, unit=2.0)
        frame(d, 'Sheet 2 — C-mode measurement path (K1 and K2 de-energised)', 2, 7)
        mcu_box(0, 7.5, 10.0, 28.5, 'STM32G474CEU6 (on WeAct module)')
        # COMP1: + = PA1 (VCAP_ADC), − = DAC3_CH1 1.65 V
        c1, cplus, cminus, cout = opamp((4.0, 21.0), 'plus', plus_top=False)
        T((c1.center[0] - 0.35, c1.center[1]), 'COMP1', loc='center', fs=FS - 1.5)
        block(0.6, 23.2, 3.4, 24.6, 'DAC3_CH1\n1.65 V', GREEN, fs=FS - 2)
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        block(2.8, 13.0, 7.2, 14.4, 'ADC1_IN2\nTIM6 + DMA stream', GREEN, fs=FS - 2)
        W((5.0, pa1[1]), (5.0, 14.4))
        mcu_pin_in(pa1, 'PA1', 'J2-7', 'ADC1_IN2 + COMP1_INP')
        mcu_pin_in((10.0, 11.0), 'PB5', 'J1-5', 'MUXC_EN (EN̄)')
        mcu_pin_in((10.0, 9.8), 'PB4', 'J1-6', 'MUXC_A1')
        mcu_pin_in((10.0, 8.6), 'PB3', 'J1-7', 'MUXC_A0')

        # U2 buffer with R29 pull-down
        y0 = cout[1]
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        dot((12.0, y0))
        two('R', (12.0, y0), (12.0, y0 - 2.6), 'R29', side='right')
        gnd((12.0, y0 - 2.6))
        T((11.0, y0 + 0.35), 'DRIVE', loc='top', color=BLUE)
        net('DRIVE', 'J2-6', 'R29-1', 'U2-2')
        net('GND', 'R29-2', 'U2-3')
        b = logic.Buf().at((14.0, y0)).anchor('in1').right()
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        net('GND', 'U3-8')
        zx = b.out[0] + 0.5
        W(b.out, (zx, y0), (zx, u3.p4[1]), u3.p4)
        T((zx + 0.15, (y0 + u3.p4[1]) / 2 + 0.1), 'C_MUX_COM', loc='right', fs=FS - 2, color=BLUE)
        net('C_MUX_COM', 'U2-4', 'U3-4')
        # control lines
        W((10.0, 11.0), (17.0, 11.0), (17.0, u3.p6[1]), u3.p6)
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            net('VCAP', f'{ref}-2')
        bus_lo = u3.p12[1]
        W((xb, bus_lo), (xb, 24.5))
        T((xb - 0.2, 24.7), 'VCAP', loc='left', color=BLUE)
        net('VCAP', 'R32-1', 'C1-1', 'C2-1', 'R33-1', 'D1-3', 'U6-4')
        # D1 clamp on VCAP (top)
        W((xb, 24.5), (32.5, 24.5))
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        W((xb, bus_lo), (xb, 11.0))
        two('R', (xb, 11.0), (xb, 8.4), 'R32', side='right')
        W((xb, 8.4), (xb, 7.8))
        T((xb, 7.6), 'VCAP_ADC → PA1 (J2-7)', loc='bottom', color=BLUE)
        net('VCAP_ADC', 'R32-2', 'J2-7')
        T((xb + 0.3, 12.2), 'also U6 (SSR3 clamp), sheet 3', fs=FS - 3, color=GREY)
        # C1 || C2 || R33 between VCAP and C_BLOCK
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        elm.Resistor().at((L, 18.2)).to((R, 18.2))
        T(((L + R) / 2, 17.55), lbl('R33') + ' (bleed)', loc='bottom', fs=FS - 2.5)
        dot((R, 20.0))
        T((R + 0.1, 20.35), 'C_BLOCK', loc='right', fs=FS - 1.5, color=BLUE)
        net('C_BLOCK', 'C1-2', 'C2-2', 'R33-2', 'K1-10')
        # K1B: NC 10 = C_BLOCK (closed), COM 9 = FH, NO 8 = not connected
        nc = (40.0, 20.0)
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        gnd(nc_a)
        net('GND', 'K1-3')
        notes(11.0, 6.6, [
            ('U3 truth table (A = B = MUXC_A0 on PB3, C = MUXC_A1 on PB4):  00 → X0 R3 98.6 kΩ   01 → X1 R2 993.6 Ω   10 → Y0 R1 98.9 Ω   11 → Y1 R4 1.01 MΩ', GREY),
            ('MUXC_EN (PB5) has R30 100 kΩ pull-up to +3V3: U3 is off at reset (EN̄ active low).', GREY),
            ('The DUT is in series with C1 ‖ C2 (C_block ≈ 1000 µF):  C_DUT = C_eq·C_block / (C_block − C_eq).', 'black'),
            ('Oscillator: COMP1 drives U2 through PA0, T = K·R·C + T0 (K ≈ 0.085), timed by TIM2.  RC step: PA0 GPIO step, ADC1 records V(t), τ = R·C.', 'black'),
        ])
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        # J6 and R12 bias feed
        vb = (11.0, 26.5)
        dot(vb)
        T((vb[0] - 0.2, vb[1] + 0.35), lbl('J6', short=True) + ':  pin 1 = V_BIAS, pin 2 = GND', loc='right', fs=FS - 1.5)
        T((vb[0] - 0.2, vb[1] - 0.4), 'V_BIAS', loc='left', color=BLUE)
        net('V_BIAS', 'J6-1', 'R12-1', 'U5-4')
        net('GND', 'J6-2')
        W(vb, (21.0, 26.5))
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        # SSR3 = U6
        u6 = ssr(17.0, 12.5, 'U6', '4', '3')
        W(u6['sw_top'], (u6['sw_top'][0], 15.3))
        T((u6['sw_top'][0] + 0.15, 15.5), 'VCAP (sheet 2)', loc='right', color=BLUE)
        two('R', u6['sw_bot'], (u6['sw_bot'][0], 10.3), 'R11', side='right', extra='1 Ω')
        gnd((u6['sw_bot'][0], 10.3))
        net('SSR3_SW', 'U6-3', 'R11-1')
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            net('GND', f'{u}-2')
        # LED drives
        pb11 = (9.0, u5['led_a'][1])
        mcu_pin_in(pb11, 'PB11', 'J2-20', 'SSR13: SSR1 + SSR3 together')
        two('R', (11.5, pb11[1]), u5['led_a'], 'R22', side='top')
        W(pb11, (11.5, pb11[1]))
        dot((10.6, pb11[1]))
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        net('SSR1_LED', 'R22-2', 'U5-1')
        net('SSR3_LED', 'R23-2', 'U6-1')
        pb13 = (9.0, u7['led_a'][1])
        mcu_pin_in(pb13, 'PB13', 'J1-19', 'SSR2_CTRL: discharge')
        W(pb13, (11.5, pb13[1]))
        two('R', (11.5, pb13[1]), u7['led_a'], 'R24', side='top')
        net('SSR2_CTRL', 'J1-19', 'R24-1')
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        dot((sh[0], 15.0))
        W((sh[0], 15.0), (35.0, 15.0))
        dot((33.0, 15.0))
        T((sh[0] - 0.2, 15.0), 'SH_DIV (÷11)', loc='left', color=BLUE)
        net('SH_DIV', 'R38-2', 'C21-2', 'R39-1', 'C20-1', 'U10-3')
        two('R', (sh[0], 15.0), (sh[0], 11.0), 'R39', side='left')
        elm.Capacitor().at((33.0, 15.0)).to((33.0, 11.0))
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        gnd((sh[0], 11.0))
        gnd((33.0, 11.0))
        net('GND', 'R39-2', 'C20-2')
        # U10: switch on the left (pin 4 top = VN_SENSE, pin 3 bottom = SH_DIV), LED right
        u10 = ssr(37.0, 12.0, 'U10', '4', '3', sw_left=True)
        W((35.0, 15.0), (35.0, 12.0), u10['sw_bot'])
        W(u10['sw_top'], (u10['sw_top'][0], 16.6), (44.0, 16.6))
        T((44.2, 16.6), 'VN_SENSE → PB0 (J2-15)', loc='right', color=BLUE)
        T((44.2, 16.0), 'OPAMP3 follower → ADC3 (sheet 4)', loc='right', fs=FS - 2.5, color=GREY)
        net('VN_SENSE', 'U10-4', 'J2-15')
        W(u10['led_a'], (u10['led_a'][0], u10['led_a'][1] + 1.0))
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        net('+3V3', 'U10-1')
        two('R', u10['led_k'], (u10['led_k'][0], 9.0), 'R43', side='right')
        W((u10['led_k'][0], 9.0), (9.0, 9.0))
        mcu_pin_in((9.0, 9.0), 'PC4', 'J2-14', 'C_MODE_SW: LOW = U10 on')
        net('U10_LED_K', 'U10-2', 'R43-2')
        net('C_MODE_SW', 'R43-1', 'J2-14')
        notes(28.5, 7.6, [
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        d.config(fontsize=FS, unit=2.0)
        frame(d, 'Sheet 4 — R-mode, 4-wire Kelvin (K1 energised, K2 energised)', 4, 7)
        mcu_box(0, 5.5, 10.0, 29.0, 'STM32G474CEU6')
        # OPAMP1 inside: − = PA3 (VREF), + = PA7 (MUXR_COM)
        o1, o1p, o1m, o1o = opamp((4.5, 24.0), 'out', plus_top=False)
        o1, o1p, o1m, o1o = opamp((7.0, 24.0), 'out', plus_top=False) if False else (o1, o1p, o1m, o1o)
        T((o1.center[0] - 0.35, o1.center[1]), 'OPAMP1', loc='center', fs=FS - 2)
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        W(o1p, (o1p[0] - 0.4, o1p[1]), (o1p[0] - 0.4, pa7[1]), pa7)
        mcu_pin_in(pa7, 'PA7', 'J2-13', 'OPAMP1 VINP2 · ADC2_IN4')
        pb14 = (10.0, 22.0)
        mcu_pin_in(pb14, 'PB14', 'J1-18', 'R_FORCE: Hi-Z in Kelvin')
        # VREF network
        n = (12.5, 27.0)
        W(pa3, n)
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        SEEN.add('C5')
        elm.Capacitor().at((16.8, 27.0)).to((16.8, 24.0))
        T((17.05, 25.5), lbl('C3'), fs=FS - 2.5)
        # OP1_OUT -> R14 -> Q1 gate ; R13 pull-up ; R15 to PB14
        W(pa2, (16.8, 24.0))
        dot((16.8, 24.0))
        two('R', (17.4, 24.0), (21.0, 24.0), 'R14', side='bottom')
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        mc = (X, 13.0)
        W((X, 13.8), mc)
        dot(mc)
        T((X + 0.25, mc[1] - 0.15), 'MUXR_COM', loc='right', fs=FS - 1, color=BLUE)
        net('MUXR_COM', 'K2-5', 'U4-4', 'J2-13')
        W(mc, (11.4, 13.0), (11.4, pa7[1]), pa7)
        T((11.6, 15.8), 'MUXR_COM (H1)', loc='right', fs=FS - 2, color=BLUE)
        # U4 below
        u4 = ic(14.5, 5.6, 'U4', [
            ('left', 'A', '11', 'MUXR_A0'), ('left', 'B', '10', 'MUXR_A0'), ('left', 'C', '9', 'MUXR_A1'),
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            net('GND', f'{ref}-2')
        W((gx, u4.p1[1]), (gx, u4.p12[1] - 0.8))
        gnd((gx, u4.p12[1] - 0.8))
        for pin, hdr, nn, anch, yy, xx in (('PB15', 'J1-17', 'MUXR_EN', 'p6', 9.6, 12.0),
                                          ('PB7', 'J1-3', 'MUXR_A1', 'p9', 8.4, 12.6),
                                          ('PB6', 'J1-4', 'MUXR_A0', 'p10', 7.2, 13.2)):
            mcu_pin_in((10.0, yy), pin, hdr, nn)
            a = getattr(u4, anch)
            W((10.0, yy), (xx, yy), (xx, a[1]), a)
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        net('MUXR_EN', 'R31-1')
        net('+3V3', 'R31-2')
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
